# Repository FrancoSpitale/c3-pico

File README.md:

# c3-pico — minimalist ESP32-C3 dev board

A no-frills ESP32-C3 development board in **KiCad 9**: USB-C with native USB,
3.3 V LDO, BOOT/RESET buttons and every usable GPIO on two breadboard-friendly
0.1" rows. Designed to be the board you actually reach for — nothing on it that
a blinky-to-production bring-up doesn't need.

| Top | Bottom |
|---|---|
|  |  |

Schematic: [docs/schematic.svg](docs/schematic.svg) · Source: [hardware/](hardware/)

## Specs

| | |
|---|---|
| MCU | ESP32-C3-WROOM-02-N4 (RIS-V, Wi-Fi + BLE, 4 MB flash) |
| USB | USB-C, native USB-Serial-JTAG (no bridge IC) |
| Power | USB 5 V → AP2112K-3.3 LDO (600 mA) |
| I/O | 13 GPIO on 2 × 1×9 headers, 1.0" apart (breadboard) |
| Board | 28.4 × 51.5 mm, 2-layer, 1.6 mm FR-4 |
| Buttons | BOOT (IO9) + RESET (EN) |
| LEDs | power (green) + user (IO8, blue) |

## Design decisions

**Module, not chip-down.** ESP32-C3-WROOM-02 (PCB antenna, pre-certified RF)
instead of a bare ESP32-C3 with discrete RF. On a hobby/prototyping board the
~US$1 premium buys you regulatory-certified radio and zero antenna-matching
risk on a 2-layer board — chip-down C3 designs want controlled impedance and a
tuned pi network that this class of board can't justify.

**Native USB only, UART on the header.** The C3's built-in USB-Serial-JTAG
(GPIO18/19) goes straight to the USB-C connector — no CP2102/CH340, which
removes a BOM line, a failure mode, and ~US$0.50. GPIO18/19 are therefore *not*
on the headers; UART0 (IO20/IO21) is, for classic serial workflows and as the
escape hatch if an application reconfigures the USB pins.

**USB-C done by the spec.** 5.1 k pulldowns on CC1/CC2 mark the board as a UFP
device, so it powers up from USB-C hosts *and* C-to-C cables/chargers (boards
that skip these only work on A-to-C cables). USBLC6-2SC6 ESD array on D+/D−.

**Strapping pins handled, not hidden.** IO9 (BOOT) has its button; IO8 gets a
10 k pull-up (required high for serial download mode) and doubles as the user
LED, Espressif-devkit style. Both are still broken out — the pull-up is weak
enough to ignore in normal use.

**EN with RC delay.** 10 k pull-up + 1 µF on EN gives a clean power-on ramp and
a proper RESET button without a supervisor chip.

**Antenna overhang + bottom ground plane.** The module hangs off the top edge so
its PCB antenna clears the board copper (with a copper keep-out under the
antenna footprint as a belt-and-suspenders measure). The stackup is the classic
2-layer arrangement — signals and power on top, an unbroken ground plane on the
bottom — so every top trace has a clean return path directly beneath it.

## Pinout

| Left (J2) | Right (J3) |
|---|---|
| 3V3 | IO0 |
| EN | IO1 |
| IO4 | IO2 |
| IO5 | IO3 |
| IO6 | IO21 (TX) |
| IO7 | IO20 (RX) |
| IO8 (LED) | IO10 |
| IO9 (BOOT) | 5V |
| GND | GND |

Header order mirrors the module's physical pin order, so the layout fans out
1:1 with no crossings.

## Fabrication

`fabrication/c3-pico-gerbers-jlcpcb.zip` uploads directly to JLCPCB: 2 layers,
1.6 mm, ENIG recommended (fine-pitch module pads). `c3-pico-bom.csv` and
`c3-pico-pos.csv` are ready for the assembly service — add LCSC part numbers at
order time. The module and USB-C are the only fine-pitch parts; everything else
is 0603 or SOT-23.

## Verification

- ERC: 0 errors, 0 warnings ([hardware/erc.rpt](hardware/erc.rpt))
- DRC: 0 errors, 0 unconnected, 0 clearance/short/edge violations, schematic
  parity OK ([hardware/drc.rpt](hardware/drc.rpt)). One remaining info-level
  notice — U1's library footprint differs from stock because the module's
  antenna silkscreen was trimmed where it overhangs the board edge (deliberate).
- Routing: placed by hand for a clean fan-out, autorouted with
  [freerouting](https://github.com/freerouting/freerouting), then hand-verified.

## Repository layout

```
hardware/     KiCad 9 project (schematic, PCB, ERC/DRC reports)
fabrication/  Gerbers zip (JLCPCB), BOM, pick & place
docs/         Renders and schematic SVG
```

## License

MIT — see [LICENSE](LICENSE). Hardware provided as-is, no warranty; review before
fabricating. Not yet fabricated — if you build one, open an issue with results.

---
*Franco Spitale, 2026. Rev 1.0.*

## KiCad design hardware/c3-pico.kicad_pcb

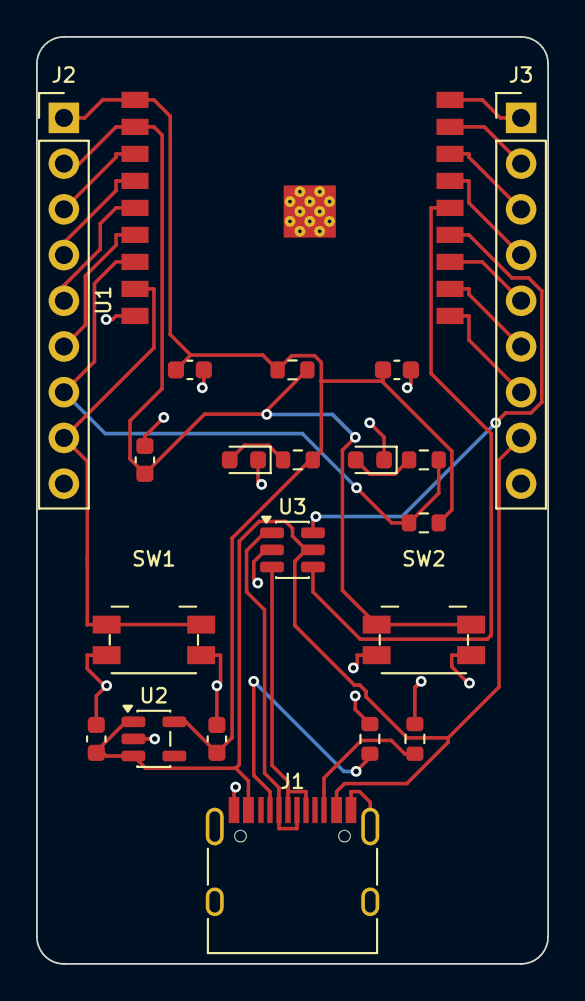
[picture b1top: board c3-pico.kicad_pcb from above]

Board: 2 copper layers, 28.4 x 51.5 mm, 21 parts (0 on the bottom side), 25 nets.

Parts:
C1: 100nF; C_0603_1608Metric
C2: 10uF; C_0603_1608Metric
C3, C4, C5: 1uF; C_0603_1608Metric
J1: USB-C; USB_C_Receptacle_HRO_TYPE-C-31-M-12
J2, J3: 1x09_Header; PinHeader_1x09_P2.54mm_Vertical
LED1: green; LED_0603_1608Metric
LED2: blue; LED_0603_1608Metric
R1, R7: 10k; R_0603_1608Metric
R3, R4: 5k1; R_0603_1608Metric
R5, R6: 1k; R_0603_1608Metric
SW1: BOOT; Panasonic_EVQPUJ_EVQPUA
SW2: RESET; Panasonic_EVQPUJ_EVQPUA
U1: ESP32-C3-WROOM-02
U2: AP2112K-3.3; SOT-23-5
U3: USBLC6-2SC6; SOT-23-6

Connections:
+3V3: C1.1, C2.1, C5.1, J2.1, R1.1, R5.2, R7.2, U1.1, U2.5
+5V: C4.1, J1.A4, J1.A9, J1.B4, J1.B9, J3.8, U2.1, U2.3, U3.5
EN: C3.1, J2.2, R1.2, SW2.1, U1.2
GND: C1.2, C2.2, C3.2, C4.2, C5.2, J1.A1, J1.A12, J1.B1, J1.B12, J1.S1, J2.9, J3.9, LED1.1, LED2.1, R3.2, R4.2, SW1.2, SW2.2, U1.9, U1.19, U2.2, U3.2
IO0: J3.1, U1.18
IO1: J3.2, U1.17
IO2: J3.3, U1.16
IO3: J3.4, U1.15
IO4: J2.3, U1.3
IO5: J2.4, U1.4
IO6: J2.5, U1.5
IO7: J2.6, U1.6
IO8: J2.7, R6.2, R7.1, U1.7
IO9: J2.8, SW1.1, U1.8
IO10: J3.7, U1.10
IO20: J3.6, U1.11
IO21: J3.5, U1.12
unnamed: J1.A5, R3.1
unnamed: J1.B5, R4.1
unnamed: J1.A6, J1.B6, U3.3
unnamed: J1.A7, J1.B7, U3.1
unnamed: LED1.2, R5.1
unnamed: LED2.2, R6.1
USB_D+: U1.14, U3.4
USB_D-: U1.13, U3.6

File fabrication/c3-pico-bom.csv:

"Designator","Value","MPN","Footprint","Qty"
"C1","100nF","CL10B104KB8NNNC","Capacitor_SMD:C_0603_1608Metric","1"
"C2","10uF","CL10A106KP8NNNC","Capacitor_SMD:C_0603_1608Metric","1"
"C3-C5","1uF","CL10A105KB8NNNC","Capacitor_SMD:C_0603_1608Metric","3"
"J1","USB-C","TYPE-C-31-M-12","Connector_USB:USB_C_Receptacle_HRO_TYPE-C-31-M-12","1"
"J2,J3","1x09_Header","","Connector_PinHeader_2.54mm:PinHeader_1x09_P2.54mm_Vertical","2"
"LED1","green","KT-0603R-GREEN","LED_SMD:LED_0603_1608Metric","1"
"LED2","blue","KT-0603R-BLUE","LED_SMD:LED_0603_1608Metric","1"
"R1,R7","10k","RC0603FR-0710KL","Resistor_SMD:R_0603_1608Metric","2"
"R3,R4","5k1","RC0603FR-075K1L","Resistor_SMD:R_0603_1608Metric","2"
"R5,R6","1k","RC0603FR-071KL","Resistor_SMD:R_0603_1608Metric","2"
"SW1","BOOT","EVQ-PUJ02K","Button_Switch_SMD:Panasonic_EVQPUJ_EVQPUA","1"
"SW2","RESET","EVQ-PUJ02K","Button_Switch_SMD:Panasonic_EVQPUJ_EVQPUA","1"
"U1","ESP32-C3-WROOM-02","ESP32-C3-WROOM-02-N4","RF_Module:ESP32-C3-WROOM-02","1"
"U2","AP2112K-3.3","AP2112K-3.3TRG1","Package_TO_SOT_SMD:SOT-23-5","1"
"U3","USBLC6-2SC6","USBLC6-2SC6","Package_TO_SOT_SMD:SOT-23-6","1"
